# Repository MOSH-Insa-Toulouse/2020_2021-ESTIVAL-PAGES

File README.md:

# LoRa Project: Smart Gas Sensor

This project is realised in the 5th year PTP ISS at INSA Toulouse. A **LoRa-connected gas sensor** has been developed to alert the user about the concentration of health threatening gas near the sensor.

# Content

This repository contains: 
* KiCad PCB files: A shield for the gas sensor to plug on an Arduino Uno (made with KiCad)
* The datasheet: Complete datasheet for the gaz sensor

## KiCad PCB Files

### Overview
The shield is composed of :

* A home-made gas sensor (made at AIME)
* An amplifier stage for home-made gas sensor
* A commercial gas sensor for the calibration of the home-made one (Grove connectors)
* A LoRa chip for the data transmission
* A LED as an on/off indicator

### Schematics

### PCB Layout

### PCB Visualisation

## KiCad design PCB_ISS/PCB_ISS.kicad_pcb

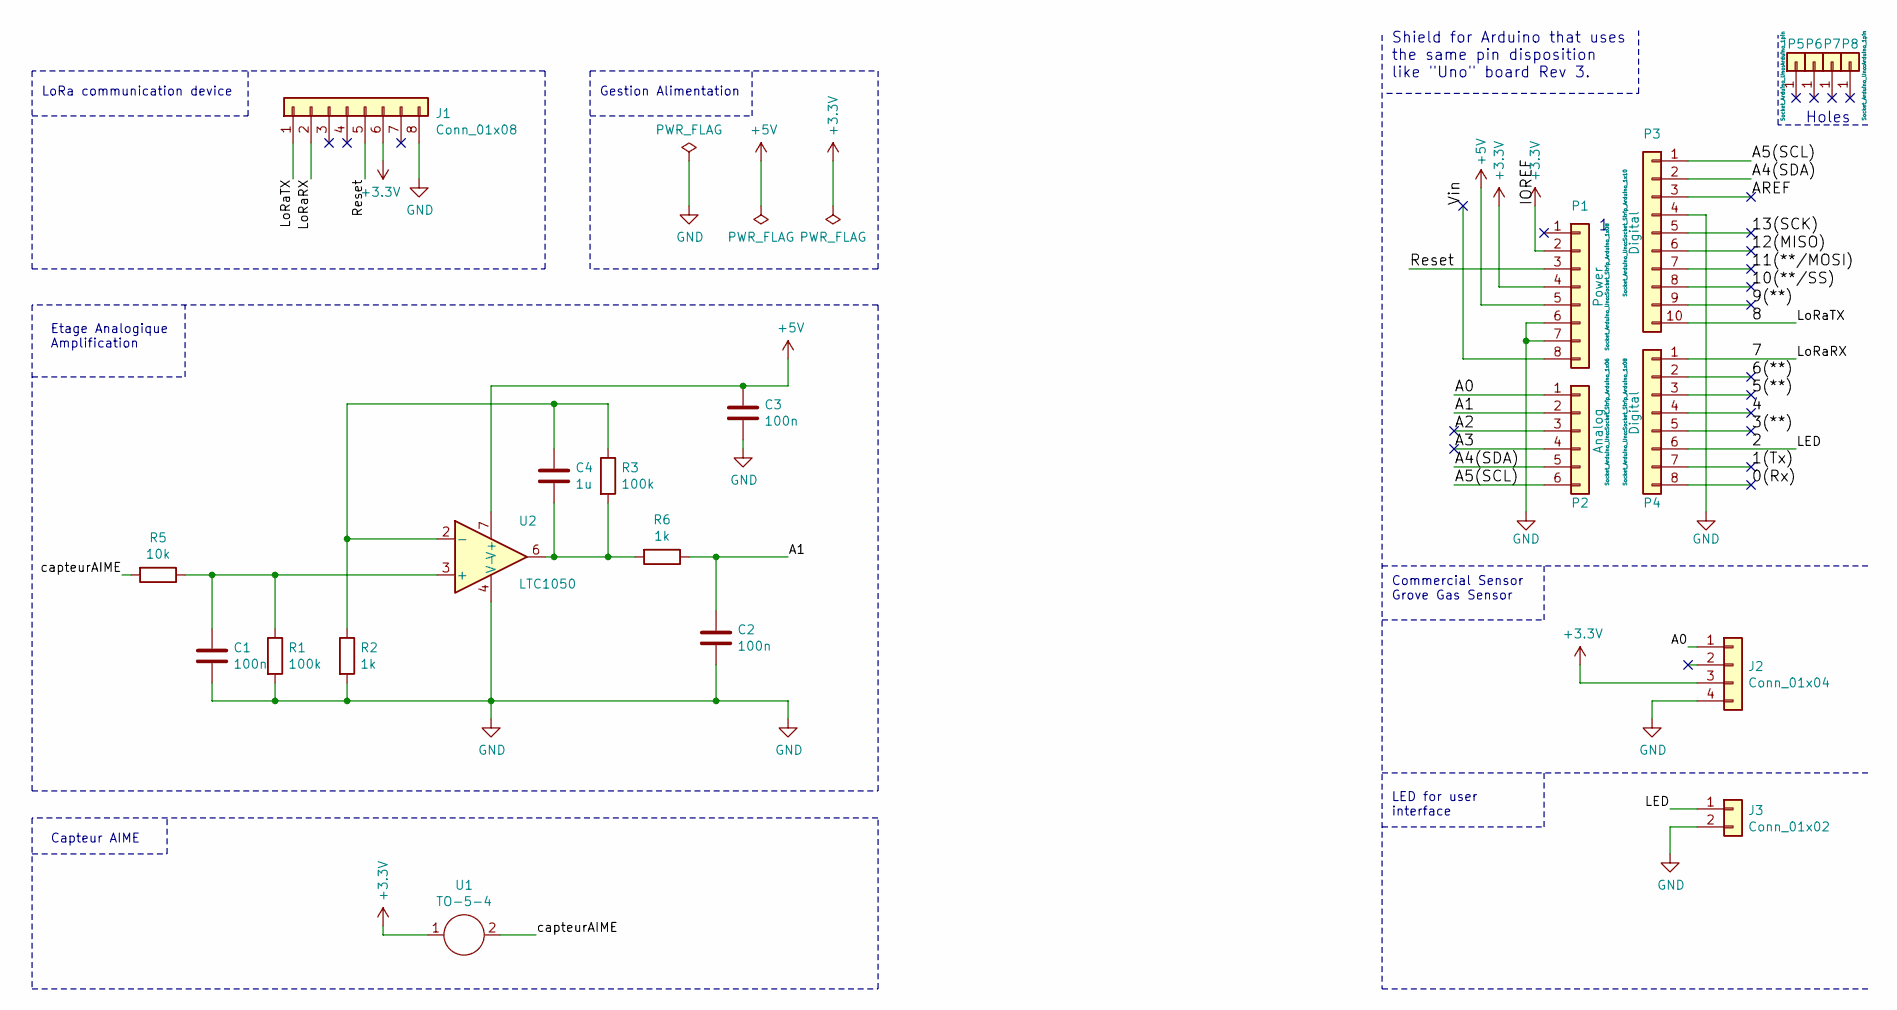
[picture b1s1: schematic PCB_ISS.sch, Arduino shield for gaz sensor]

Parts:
C1, C2, C3: 100n; C_Disc_D6.0mm_W2.5mm_P5.00mm
C4: 1u; C_Disc_D6.0mm_W2.5mm_P5.00mm
J1: Conn_01x08; Module_RN2483_Breakout_WITHOUTPADS
J2: Conn_01x04; conn_Grove
J3: Conn_01x02; conn_LED
P1: Power; Socket_Strip_Arduino_1x08
P2: Analog; Socket_Strip_Arduino_1x06
P3: Digital; Socket_Strip_Arduino_1x10
P4: Digital; Socket_Strip_Arduino_1x08
P5, P6, P7, P8: CONN_01X01; Arduino_1pin
R1, R3: 100k; R_Axial_DIN0204_L3.6mm_D1.6mm_P5.08mm_Vertical
R2, R6: 1k; R_Axial_DIN0204_L3.6mm_D1.6mm_P5.08mm_Vertical
R5: 10k; R_Axial_DIN0204_L3.6mm_D1.6mm_P5.08mm_Vertical
U1: TO-5-4
U2: LTC1050; DIP-8_W7.62mm_LongPads

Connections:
+3V3: J1.6, J2.3, P1.2, P1.4, U1.1
+5V: C3.1, P1.5, U2.7 (V+)
/0(Rx): P4.8
/1(Tx): P4.7
/2: J3.1, P4.6
/3(**): P4.5
/4: P4.4
/5(**): P4.3
/6(**): P4.2
/7: J1.2, P4.1
/8: J1.1, P3.10
/9(**): P3.9
/10(**/SS): P3.8
/11(**/MOSI): P3.7
/12(MISO): P3.6
/13(SCK): P3.5
/A0: J2.1, P2.1
/A1: C2.1, P2.2, R6.1
/A2: P2.3
/A3: P2.4
/A4(SDA): P2.5, P3.2
/A5(SCL): P2.6, P3.1
/AREF: P3.3
/Reset: J1.5, P1.3
/Vin: P1.8
/capteurAIME: R5.2, U1.2
GND: C1.2, C2.2, C3.2, J1.8, J2.4, J3.2, P1.6, P1.7, P3.4, R1.2, R2.2, U2.4 (V-)
unnamed: C1.1, R1.1, R5.1, U2.3 (+)
unnamed: C4.1, R2.1, R3.1, U2.2 (-)
unnamed: C4.2, R3.2, R6.2, U2.6

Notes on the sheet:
Holes
Shield for Arduino that uses the same pin disposition like "Uno" board Rev 3.
Etage Analogique Amplification
Commercial Sensor Grove Gas Sensor
LoRa communication device
Gestion Alimentation
Capteur AIME
LED for user interface

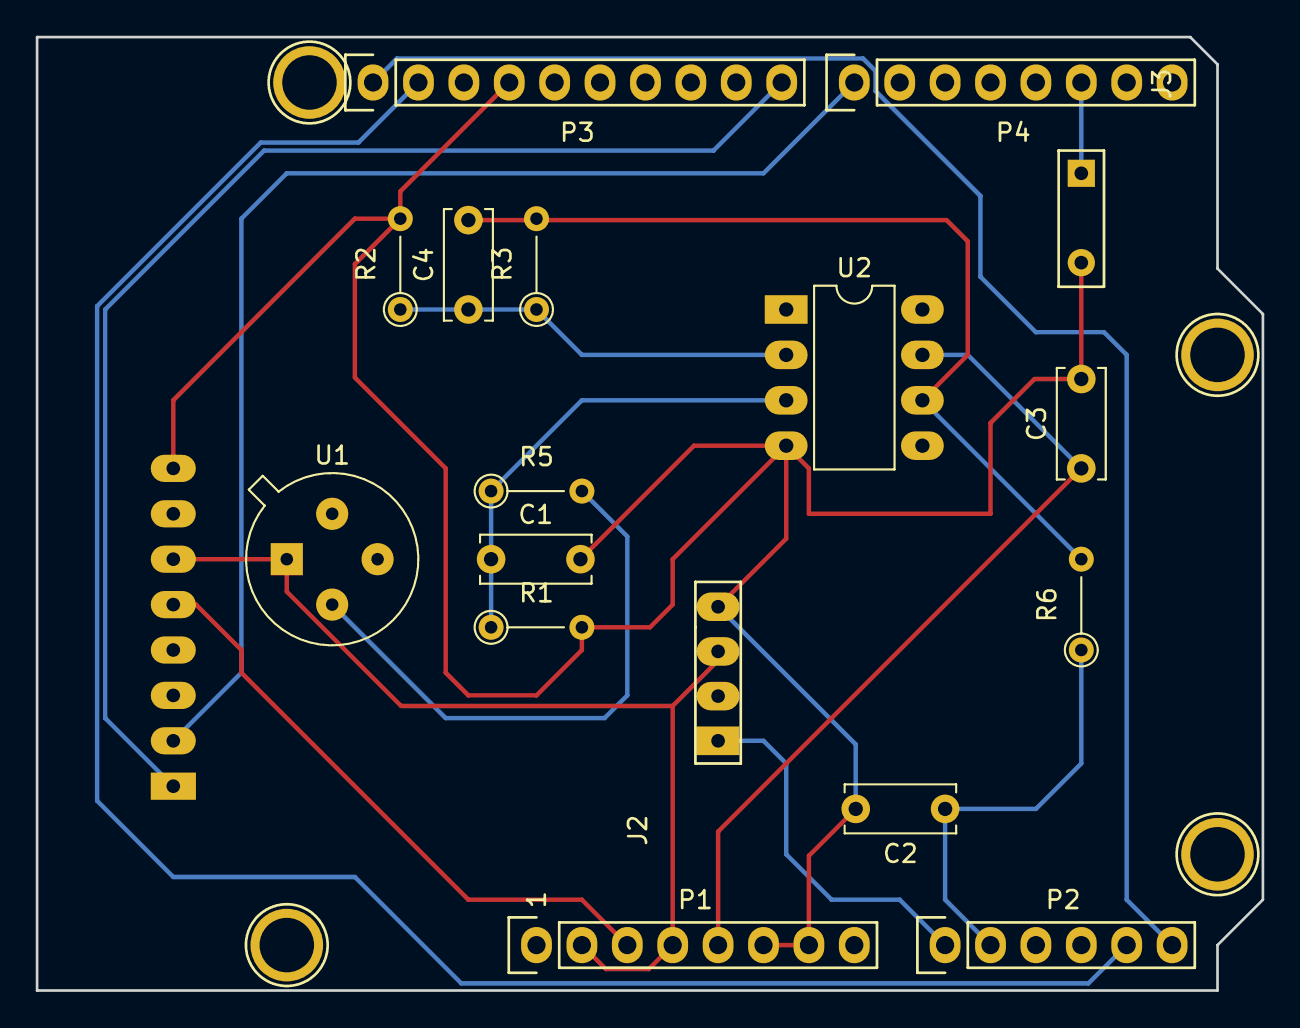
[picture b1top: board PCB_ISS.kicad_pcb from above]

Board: 2 copper layers, 68.6 x 53.3 mm, 22 parts (0 on the bottom side), 15 nets.
